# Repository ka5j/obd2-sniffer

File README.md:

# OBD2 CAN Sniffer

A read-only scanner for a car's diagnostic port. It records the messages between the car's computers,
asks the engine computer for live data, trouble codes and the VIN, and shows it all on a laptop. It
only ever asks standard questions, and can't change anything in the car.

Today it runs on an STM32 development board, against a simulated engine computer. The goal is its own
custom circuit board that plugs straight into the car.

## Where it stands

| | |
|---|---|
| **Works today** | On a development board with no car: CAN capture with nothing lost unnoticed, OBD2 live data, trouble codes and VIN, a transmit guard, crash recovery, and a desktop app and command line |
| **Not done yet** | It hasn't been on a real CAN bus or in a real car |
| **The goal** | A custom circuit board that plugs into the car, powered from the laptop, with a hardware switch that turns the transmitter off. It is in design, not built |

The full list is in [Project status](#project-status).

## Try it, no hardware needed

The laptop software includes a simulator of the whole board. You need Python 3.10 or newer (the one
that comes with macOS can be too old: see [Getting started](docs/getting-started.md#level-1-try-it-no-hardware)),
and Git:

```sh
git clone https://github.com/ka5j/obd2-sniffer.git
cd obd2-sniffer
python3 -m venv .venv
source .venv/bin/activate          # Windows: .venv\Scripts\activate
pip install -e "host[gui]"         # the desktop app's Qt library is a large download
obdsniff --port sim gui
```

Press **Connect**, open the **OBD2** tab, and press **Start**.

To go further, with a real board and ready-made firmware, or building from source, see
[Getting started](docs/getting-started.md).

## How it works

A car's computers share one pair of wires, the **CAN bus**, and the **OBD2 port** under the dashboard
is the way in. On the bus, every computer sees every message. So a tool can listen to it all, and ask
the engine computer standard questions such as "what is the engine speed?".

With no car, the development board plays both sides:

```mermaid
flowchart LR
    Laptop["Laptop<br/>desktop app or command line"] <-- "USB cable" --> Tool
    subgraph Board["Development board (NUCLEO-F446RE)"]
        Tool["Scan tool firmware"] <--> CAN["CAN controller<br/>in loopback"]
        ECU["Simulated engine computer"] <--> CAN
    end
```

1. The **laptop** asks one question at a time, and shows the answers.
2. The **firmware** sends each question through its CAN controller, timestamps and numbers every
   message it receives, and sends them to the laptop.
3. The **CAN controller** runs in loopback: it receives its own messages and nothing leaves the chip,
   so a simulated engine computer on the same board can answer through real CAN hardware.

[How it works](docs/how-it-works.md) explains all of this from the beginning, with no car knowledge
assumed.

## Why it's worth a look

- **Nothing is lost unnoticed.** Every message is timestamped to the microsecond and numbered the
  moment it arrives. Measured on the board in loopback: 100,000 messages at 100% network load, none
  lost. When traffic outgrows the USB link, every dropped message is counted and reported.
- **Read-only by design.** The board asks only when the laptop tells it to, and every frame it sends
  passes a transmit guard that allows only read requests, at most 20 a second. Clearing a trouble code
  isn't built in. [The safety design](docs/design/safety.md) adds a hardware switch, and lists the
  risks that remain.
- **Recovers from crashes and says why.** A watchdog restarts the board if the program stops
  responding, and a crash handler records the fault type and code address, then reports them after
  the restart.
- **Tested to safety-critical standards.** The core logic is unit-tested to 100% MC/DC coverage, the
  coverage standard used for flight-control software, and all C code follows the MISRA C:2012 rules
  used in the automotive industry, with every exception documented. See the
  [live quality report](https://ka5j.github.io/obd2-sniffer/).
- **Requirements with a test for each.** What the device must do, survive and never do is written
  down as [numbered requirements](docs/design/requirements.md), each with its test and its honest
  status today.
- **Every release is checked on the board.** The published files are built by CI from the tag, then
  flashed onto the board and checked before they go out.

## Where to go next

| You want to... | Read |
|---|---|
| Understand how it works, from the beginning | [How it works](docs/how-it-works.md) |
| Run it, with or without a board | [Getting started](docs/getting-started.md) |
| Use the desktop app, command line or Python library | [The laptop tool](host/README.md) |
| Judge the engineering | [Safety](docs/design/safety.md), [requirements](docs/design/requirements.md), [testing](docs/design/testing.md) and [how the firmware fits together](docs/design/architecture.md) |
| See the circuit board design | [Circuit board](docs/design/circuit-board.md) and [the design files](hardware/README.md) |
| See every document | [Documentation](docs/README.md) |

## Measured on the board

All of these are in loopback, on a development board.

| What | Result |
|---|---|
| CAN capture, 500 kbit/s at 100% load | 100,000 messages, 0 lost, 0 damaged |
| CAN overload, 1 Mbit/s at 100% load (Release build) | The bus outruns the USB link: 5,209 of 20,000 dropped, each one counted on the board and seen as a gap on the laptop. With streaming off, 0 dropped |
| Commands while the CAN bus is full | 2,623 commands as 42,127 messages arrived, none failed, no byte lost |
| OBD2 against the simulated engine computer | 201 requests in 10 s (the transmit guard allows at most 20 a second), every one answered, 0 timeouts, 0 refused by the guard; none once the laptop stops asking |
| Longest CAN receive interrupt | 6 to 9 µs in the Release build and 10 to 14 µs in Debug across runs, with OBD2 traffic (the time includes serial interrupts that preempt it), against 238 µs between messages at full load |
| Watchdog | A stuck board restarts after 535 ms and reports why |

How each number was measured: [testing.md](docs/design/testing.md#checks-on-the-board).

## Topics covered by this project

| Area | Details |
|---|---|
| Embedded C | Bare-metal firmware on an Arm Cortex-M4, no operating system |
| Microcontroller peripherals | Clocks, UART serial, DMA, timers, interrupts, watchdog, CAN controller |
| Automotive protocols | CAN, OBD2 (SAE J1979), ISO-TP multi-frame transport |
| Reliability | Watchdog, crash capture and reporting, interrupt priorities set by deadline, flow control |
| Safety engineering | Numbered requirements each with a test, a layered read-only safety design with a hardware interlock, failure-mode analysis (FMEA) |
| Python | Desktop app (PySide6), command-line tool, serial communication, board simulator |
| Code quality | MISRA C:2012 compliance with documented deviations, static analysis (cppcheck), worst-case stack analysis |
| Testing and tooling | Unit tests in C (Unity) and Python, 100% MC/DC coverage, sanitizers, CMake, GitHub Actions CI, Git branching workflow |

## Repository layout

| Folder | What's in it |
|---|---|
| [`firmware/`](firmware) | STM32 firmware, one folder per subsystem: `system`, `console`, `can`, `obd`, `fault` (and `hal`, ST's driver settings) |
| [`lib/`](lib) | Portable C with no hardware code: buffers, link encoding, console logic, CAN timing, ISO-TP, OBD2 and the transmit guard. Compiled into the firmware and unit-tested on a laptop |
| [`tests/`](tests) | C unit tests, in the same folders as `lib/` |
| [`host/`](host) | The laptop tool `obdsniff`: command line, desktop app, board simulator |
| [`scripts/`](scripts) | Board check, coverage, MISRA and stack-use gates, quality report, screenshots, release-file and link checks |
| [`hardware/`](hardware/README.md) | Circuit board design files, in KiCad, and the revision A brief. The design isn't started yet |
| [`docs/`](docs) | [All the documents](docs/README.md) |
| [`misra/`](misra) | MISRA policy: every deviation and its reason |

## Project status

| Part | Status |
|---|---|
| Build system, project structure, automated builds (CI) | Done |
| Microcontroller start-up: 168 MHz clock, start-up report, reset-cause reporting | Done, verified on hardware |
| Serial link to the laptop: interrupt and DMA driven, one command protocol, board commands | Done, verified on hardware |
| Watchdog and crash capture with reports after restart | Done, verified on hardware |
| Laptop tool: command line, interactive shell, board simulator | Done, verified on hardware |
| Laptop tool: desktop app with board status, controls and console | Done, verified on hardware |
| Unit tests with 100% MC/DC coverage gate, published test and coverage reports | Done |
| MISRA C:2012 compliance check in CI, published compliance report | Done |
| Worst-case stack use worked out and checked in CI | Done |
| Capturing CAN messages and streaming them to the laptop | Done (tested in loopback), verified on hardware |
| OBD2 requests: live data, VIN, trouble codes, from a simulated engine computer in loopback | Done, verified on hardware |
| Transmit guard: only read requests, rate limited, sent only when the laptop asks | Done (tested in loopback), verified on hardware |
| Requirements, read-only safety design, failure-mode analysis, circuit board design | Done (written down; see [Documentation](docs/README.md)) |
| Real CAN bus on the desk with two transceivers, bus fault tests | Not started |
| USB straight from the microcontroller, with no programmer chip in between | Not started |
| Silent bit-rate detection and the bus-error latch | Not started |
| Circuit board revision A: schematic, layout, bring-up | In design: schematic checked, parts placed on the board, routing next |
| Testing in a real car | Not started |
| Circuit board revision B: the device that plugs into the car | Not started |

## License

MIT. See [LICENSE](LICENSE).

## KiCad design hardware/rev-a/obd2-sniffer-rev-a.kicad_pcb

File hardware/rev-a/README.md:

# Revision A: working brief

Part of the [project documentation](../../docs/README.md). The folder's guide is [here](../README.md), and
[the circuit board](../../docs/design/circuit-board.md) explains why each block exists.

**Status: parts placed on the board, nothing routed.** The schematic is drawn and its
[review](schematic-review.md) found no wiring error. The [board](#the-board) has its outline, layers, rules and every
part placed, with no copper tracks yet. Three datasheets are still unread and no one outside the project has reviewed
the design.

The schematic can be read without KiCad in [obd2-sniffer-rev-a.pdf](obd2-sniffer-rev-a.pdf), which is exported from
the KiCad files each time they change.

## In short

Revision A is the first board, built for bring-up and testing rather than to be small. It has room to probe, test points
on every important signal, and a debug header. Its mistakes get fixed in revision B, the finished plug-in device.

This page is the working sheet: the decisions, the parts and the datasheet each one was checked against, the pins, and
the checklist to complete before ordering. Everything on it can change, except the safety rules.

## Decisions

| Decision | Choice | Reason |
|---|---|---|
| Power | USB only. No connection to the car's 12 V (OBD2 pin 16) | The board only works with a laptop attached, and the laptop supplies 5 V. Removes the battery voltage from the board |
| CAN transceiver | One with a silent pin, not a standby pin | Silent mode keeps the receiver fully working with the transmitter off. A standby pin would stop normal receiving too |
| Silent-pin default | A 4.7 k resistor to 3.3 V on the board | The transceiver's internal resistor pulls the pin low, which selects "able to transmit". The board's resistor has to win, also against the microcontroller's own 30 to 50 k pull-down if firmware turned it on by mistake: the signal then still sits at 2.8 V, above the 2.31 V the transceiver needs |
| Silent signal | One signal for both transceivers | The self-test then needs the switch in OBD, which also tests the switch. One pin, one light |
| TX light | Switched by a transistor from the silent signal, through a 100 k gate resistor | The light can't load the signal, and can't be lit by firmware alone. The resistor keeps a short inside the transistor from pulling the signal low |
| Self-test connection | CAR/TEST jumpers: two 3-pin headers, one for each bus wire, placed apart | CAN2 can't reach the car connector in any position. One 2 x 3 block was rejected: a jumper cap put on sideways would short the car's two CAN wires together |
| Termination | CAN1: solder jumper, open by default. CAN2: fitted | The car's bus has its own. The self-test bus uses CAN2's |
| USB fuse | A chip fuse, not a resettable one | Lower resistance, so the transceivers' 5 V stays above their 4.5 V minimum |
| Car connector | 3 screw terminals: CANH, CANL, ground | Wiring can be checked. There is no terminal for pin 16 |

## Blocks and requirements

Every part on the board has to trace to a [requirement](../../docs/design/requirements.md).

| Block | Serves | Schematic drawn? |
|---|---|---|
| USB-C: power, fuse, data and ESD protection | PWR-5, LNK-3, USE-4 | Yes: `usb-power.kicad_sch` |
| 3.3 V regulator, PWR light | PWR-5, USE-3 | Yes: `usb-power.kicad_sch` |
| Microcontroller: crystal, decoupling, reset, BOOT0, SWD header | USE-4 | Yes: `microcontroller.kicad_sch` |
| CAN1 transceiver, ESD protection, termination solder jumper, car connector | CAN-1, CAN-6, PWR-8 | Yes: `can.kicad_sch` |
| CAN2 transceiver and CAR/TEST jumpers | CAN-7 | Yes: `can.kicad_sch` |
| LISTEN/OBD switch, silent signal, TX light | SAF-3, USE-3 | Yes: `can.kicad_sch` |
| BUS light | USE-3 | Yes: `microcontroller.kicad_sch` |
| Test points, debug serial header | Revision A only | Yes: on all three sheets |

## Parts

"Read" means the maker's datasheet was read for this design and the values below come from it.

| Part | Number | Why this one | Datasheet | Read? |
|---|---|---|---|---|
| Microcontroller | STM32F446RET6, LQFP64 | Same chip as the development board | [ST, DS10693 rev. 11](https://www.st.com/resource/en/datasheet/stm32f446re.pdf), with application notes AN4488 rev. 7, AN2606 rev. 71 and AN2867 rev. 25 | Yes |
| CAN transceiver, 2 of | TJA1051T/3, SO8 | Silent pin; 3.3 V logic supply; bus pins withstand -58 to +58 V; transmit timeout 0.3 to 5 ms; disconnects from the bus when unpowered (leakage at most 5 µA) | [NXP, rev. 9](https://www.nxp.com/docs/en/data-sheet/TJA1051.pdf) | Yes |
| CAN ESD protection | NUP2105L, SOT-23 | Working voltage 24 V and breakdown at least 26.2 V, so a short to a 16 V battery doesn't make it conduct; 30 kV contact ESD | [onsemi, rev. 12](https://www.onsemi.com/pdf/datasheet/nup2105l-d.pdf) | Yes |
| 3.3 V regulator | AP2112K-3.3, SOT-23-5 | 600 mA; input up to 6.5 V absolute; stable with 1 µF ceramic capacitors in and out | [Diodes, rev. 2-2](https://www.diodes.com/assets/Datasheets/AP2112.pdf) | Yes |
| USB ESD protection | USBLC6-2SC6, SOT-23-6 | Made for USB data pairs: at most 3.5 pF per line, 8 kV contact ESD, and it protects the 5 V line too | [ST, DS4260 rev. 7](https://www.st.com/resource/en/datasheet/usblc6-2.pdf) | Yes |
| USB-C socket | GCT USB4105-GF-A, 16 pins | USB 2.0 pins only; VBUS contacts rated 5 A together; 20,000 matings; a footprint ships with KiCad | [GCT](https://gct.co/files/drawings/usb4105.pdf) | Yes |
| USB fuse | Bourns SF-1206F100-2, 1 A fast, 1206 | 0.132 ohm typical, so about 35 mV lost at 250 mA; rated 63 V, interrupts 50 A | [Bourns](https://www.bourns.com/docs/product-datasheets/sf-1206f.pdf) | Yes |
| Resistors, capacitors, PWR light | 0603 (4.7 µF: 0805), capacitors X7R 16 V | Large enough to rework by hand on a test board | | |
| Crystal | ECS ECS-80-10-30B-TR: 8 MHz, 10 pF load, 5.0 x 3.2 mm | At most 100 ohm, where 3.2 x 2.5 mm crystals at 8 MHz reach 400 ohm; pads 2 and 4 are ground | [ECS](https://ecsxtal.com/store/pdf/ECX-53B.pdf) | Yes |
| Reset and boot buttons | C&K PTS645 type, 6 mm | A footprint ships with KiCad | | Not yet: read when the footprint is checked at layout |
| TX light transistor | onsemi BSS84, SOT-23 | P-channel; gate leakage at most 10 nA, so it doesn't load the silent signal; turns on between 0.8 and 2.0 V below 3.3 V | [onsemi, rev. 5](https://www.onsemi.com/pdf/datasheet/bss84-d.pdf) | Yes |
| LISTEN/OBD switch | C&K JS102011SAQN slide switch | Two positions; a footprint ships with KiCad | | Not yet. The schematic assumes pin 2 is the common pin and that it breaks one contact before making the other |
| Car connector | Phoenix Contact MKDS 1,5/3-5,08, 3 screw terminals | A footprint ships with KiCad | | Not yet |
| CAR/TEST and other headers | 2.54 mm pin headers, with two jumper caps | | | |

**Figures the design relies on, from the datasheets read**

| Figure | Value | Used for |
|---|---|---|
| TJA1051 silent pin | High is silent, low is normal. Internal pull-down, 1 to 10 µA at the pin | The board's pull-up and the switch |
| TJA1051 supply | 4.5 to 5.5 V. Below its undervoltage level (3.5 to 4.5 V) it disconnects from the bus | The 5 V budget from USB |
| TJA1051 supply current | At most 70 mA each while sending a dominant bit, 10 mA idle | The USB power budget |
| TJA1051 logic supply | 2.8 to 5.5 V | Runs from the 3.3 V rail |
| USB 5 V budget | 4.75 V at the laptop's port, less the cable, socket and fuse: about 4.6 V at the transceivers, against their 4.5 V minimum | Choosing a low-resistance fuse. On a weak port the transceivers disconnect from the bus, which is the safe direction |
| TX light against the silent pin | The transceiver is certainly silent above 2.31 V and certainly able to transmit below 0.99 V. The light is certainly on below 1.3 V | Between about 1.3 and 2.3 V the board could be able to transmit with the light dark. The signal is driven to 0 or 3.3 V, and no single fault found leaves it in between (fault table in the pull request that added the CAN sheet) |
| AP2112 heat | 184 °C/W in SOT-23-5 | (5.25 - 3.3) V at the worst-case 120 mA is 0.23 W, about 43 °C of rise |
| Charge taken at plug-in | About 42 µC if every capacitor on the board charges at once, against 50 µC (10 µF at 5 V) allowed by USB 2.0 | C1 on the 5 V rail is 1 µF, not 4.7 µF ([schematic review](schematic-review.md#charge-taken-at-plug-in)) |
| STM32F446 core capacitor | LQFP64 has one VCAP pin: a single 4.7 µF ceramic, ESR under 1 ohm | The microcontroller sheet. Larger packages use two 2.2 µF instead |
| STM32F446 decoupling | 100 nF at each VDD pin plus one 4.7 µF; 100 nF plus 1 µF on VDDA; VBAT to VDD with 100 nF; 100 nF on NRST | The microcontroller sheet |
| STM32F446 crystal | 4 to 26 MHz. The crystal's critical gain must stay under 1 mA/V | Choosing the crystal and its load capacitors |
| Crystal start-up margin | Critical gain 4 x 100 ohm x (2 pi x 8 MHz)^2 x (5 pF + 10 pF)^2 = 0.23 mA/V, against the chip's 1 mA/V limit: a margin of about 22, where ST asks for 5 or more | Choosing the crystal. An 18 pF crystal of 400 ohm would have failed this check |
| Crystal load capacitors | 2 x (10 pF load - 5 pF stray) = 10 pF each. The stray figure is an estimate | Checked on the built board by measuring the clock |
| STM32F446 USB bootloader | Needs a crystal that is a whole number of MHz, and prefers a low one such as 8 MHz. Entered with BOOT0 high and PB2 low. No pull-up resistor needed on the data lines | The 8 MHz crystal, the BOOT0 button and a pull-down on PB2 |
| STM32F446 bootloader pins | In bootloader mode the chip drives or pulls PA4 to PA10, PB5, PB6, PB9 to PB15, PC7 and PC9 to PC11 | The silent-signal pin must not be one of these, or the bootloader could enable the transmitter |

## Bill of materials

Exported from the schematic with `kicad-cli sch export bom`: 52 parts on 28 lines. Capacitors are X7R, 16 V, unless marked.
A blank maker means any maker's part of that value and size. The ten test-point pads and the solder jumper are
copper shapes on the board, not parts, so they aren't listed.

| Parts | Count | Value | KiCad footprint | Maker and part number |
|---|---|---|---|---|
| C1, C2, C3, C11 | 4 | 1uF 16V | `C_0603_1608Metric` |  |
| C4, C5, C6, C7, C9, C10, C15, C16, C17, C18, C19 | 11 | 100nF | `C_0603_1608Metric` |  |
| C8, C12 | 2 | 4.7uF 16V | `C_0805_2012Metric` |  |
| C13, C14 | 2 | 10pF C0G | `C_0603_1608Metric` |  |
| D1 | 1 | Green, PWR | `LED_0603_1608Metric` |  |
| D2 | 1 | Yellow, BUS | `LED_0603_1608Metric` |  |
| D3 | 1 | Red, TX | `LED_0603_1608Metric` |  |
| D4 | 1 | NUP2105L | `SOT-23` | onsemi NUP2105LT1G |
| F1 | 1 | 1A fast | `Fuse_1206_3216Metric` | Bourns SF-1206F100-2 |
| J1 | 1 | USB4105-GF-A | `USB_C_Receptacle_GCT_USB4105-xx-A_16P_TopMnt_Horizontal` | GCT USB4105-GF-A |
| J2 | 1 | Pin header | `PinHeader_1x06_P2.54mm_Vertical` |  |
| J3, JP1, JP2 | 3 | Pin header | `PinHeader_1x03_P2.54mm_Vertical` |  |
| J4 | 1 | CANH CANL GND | `TerminalBlock_Phoenix_MKDS-1,5-3-5.08_1x03_P5.08mm_Horizontal` | Phoenix Contact MKDS 1,5/3-5,08 |
| Q1 | 1 | BSS84 | `SOT-23` | onsemi BSS84 |
| R1, R2 | 2 | 5.1k | `R_0603_1608Metric` |  |
| R3, R6, R8 | 3 | 1k | `R_0603_1608Metric` |  |
| R4, R5 | 2 | 10k | `R_0603_1608Metric` |  |
| R7 | 1 | 4.7k | `R_0603_1608Metric` |  |
| R9, R10 | 2 | 120R | `R_0805_2012Metric` |  |
| R11 | 1 | 100k | `R_0603_1608Metric` |  |
| SW1, SW2 | 2 | Push button | `SW_SPST_PTS645Sx43SMTR92` |  |
| SW3 | 1 | LISTEN/OBD | `SW_SPDT_CK_JS102011SAQN` | C&K JS102011SAQN |
| TP11 | 1 | Test point, wire loop | `TestPoint_Loop_D2.50mm_Drill1.0mm` |  |
| U1 | 1 | USBLC6-2SC6 | `SOT-23-6` | STMicroelectronics USBLC6-2SC6 |
| U2 | 1 | AP2112K-3.3 | `SOT-23-5` | Diodes Incorporated AP2112K-3.3TRG1 |
| U3 | 1 | STM32F446RET6 | `LQFP-64_10x10mm_P0.5mm` | STMicroelectronics STM32F446RET6 |
| U4, U5 | 2 | TJA1051T/3 | `SOIC-8_3.9x4.9mm_P1.27mm` | NXP TJA1051T/3 |
| Y1 | 1 | 8MHz 10pF | `Crystal_SMD_5032-4Pin_5.0x3.2mm` | ECS ECS-80-10-30B-TR |

## The board

| Item | Choice | Reason |
|---|---|---|
| Size | 80 x 56 mm, corners rounded at 2 mm, four M3 mounting holes | Room to probe. Standoffs keep the pins underneath off the desk |
| Layers | 4, 1.6 mm thick. Planned use: signals, ground, power, signals | A solid ground layer under the USB and CAN signals |
| Parts | All on the top side | One assembly pass, and nothing hidden when probing |
| Smallest track and gap | 0.15 mm | Any board maker can build it. The chosen maker's own rules are confirmed before ordering |
| Smallest via | 0.6 mm with a 0.3 mm hole | Same |
| Copper to board edge | 0.3 mm | Same |

**Where things are, and why**

| Area | Parts | Reason |
|---|---|---|
| Left edge | USB-C socket, its ESD protection right behind it | A discharge is clamped at the connector. The microcontroller is turned so its USB pins face the socket |
| Top left | Fuse, 3.3 V regulator, PWR light | Power comes in at the left and flows right |
| Centre | Microcontroller, a capacitor beside each supply pin, the crystal beside its two pins | Short paths for the supply and the clock |
| Top edge | SWD and debug serial headers | Reachable with the board flat on a desk |
| Bottom edge | BOOT and RESET buttons, LISTEN/OBD switch with the TX light beside it | The switch's lever overhangs the edge. The light sits next to the control it reports on |
| Right | The two transceivers, CAR/TEST headers, ESD protection, screw terminal on the edge | The car side is kept together and away from USB. The two CAR/TEST headers are 5.5 mm apart, so one jumper cap can't bridge them |

**Checks on the board file**

| Check | Result |
|---|---|
| Board against schematic (`kicad-cli pcb drc --schematic-parity`) | 0 differences |
| Overlapping parts, clearances, holes | 0 violations |
| Connections not yet routed | 150, as expected before routing |
| Silkscreen | 19 warnings: part labels overlap each other or the board edge. Labels are arranged in the last layout step |
| Footprints against each datasheet's pad drawing | Not done yet |

One rule is relaxed, in `obd2-sniffer-rev-a.kicad_dru`: the USB-C socket's two locating pegs sit 0.19 mm from its own
ground pads, which is how GCT's pad drawing for the part has them. Every other hole keeps 0.25 mm.

The switch's position at the edge is taken from KiCad's footprint, because its datasheet is still unread.

## Microcontroller pins

Pin numbers are for LQFP64. Each was checked in ST's datasheet (table 10) and matches KiCad's symbol for the chip.

| Function | Pin (LQFP64 number) | Where it comes from |
|---|---|---|
| CAN1 receive, transmit | PB8 (61), PB9 (62) | Used by the firmware today ([`board.h`](../../firmware/system/board.h)) |
| Debug serial TX, RX (USART2) | PA2 (16), PA3 (17) | Used by the firmware today ([`board.h`](../../firmware/system/board.h)) |
| CAN2 receive, transmit | PB12 (33), PB13 (34) | Reserved ([pin assignments](../../docs/design/hardware.md#pin-assignments)) |
| USB data D-, D+ | PA11 (44), PA12 (45) | Fixed by the chip's USB peripheral |
| SWD debug SWDIO, SWCLK | PA13 (46), PA14 (49) | Fixed by the chip |
| Crystal in, out | PH0 (5), PH1 (6) | Fixed by the chip |
| BOOT0, BOOT1, reset | BOOT0 (60), PB2 (28), NRST (7) | Fixed by the chip |
| Silent-signal control | PC6 (37) | Chosen: the bootloader leaves it alone, so it floats and the board's pull-up keeps the transceivers silent |
| BUS light | PC8 (39) | Chosen: not used by the bootloader |

## What the firmware will need for this board

None of it is built yet.

- **Crystal:** the firmware expects an 8 MHz clock from the development board's programmer. An 8 MHz crystal needs one
  setting changed ([clock tree](../../docs/design/build-and-boot.md#clock-tree)).
- **Pins:** a board definition for revision A beside the development board's.
- **New drivers:** native USB, CAN2, the silent-signal control and the BUS light.
- **USB:** the board has no VBUS signal on PA9, so the USB driver must not wait for one. It must declare the current
  the board draws: 340 mA at worst.
- **No user button:** the development board's button goes away, along with its event.

## Before ordering

**The design**
- [ ] ERC and DRC pass, and every exclusion has a written reason ([design checks](../README.md#design-checks))
- [ ] Every part in the table above has a reason and a read datasheet, and is in stock
- [x] Every microcontroller pin in the schematic matches the pin table above
- [ ] Every footprint checked against its datasheet, and the board checked in KiCad's 3D view
- [ ] Reviewed by someone outside the project

**The safety rules** ([safety.md](../../docs/design/safety.md))
- [ ] No net on the board connects to OBD2 pin 16, and the car connector has only CANH, CANL and ground
- [ ] The silent signal is pulled to silent on the board, so a reset, crash or blank chip means silent
- [ ] In LISTEN, the switch stops the firmware enabling the transmitter, however the firmware behaves
- [ ] The TX light is switched by the silent signal itself, not by firmware
- [ ] CAN1's transceiver has a dominant timeout, and its bus pins withstand a short to the car's battery
- [ ] CAN1's termination is open by default
- [ ] No position of the CAR/TEST jumpers connects CAN2 to the car connector

**The rule for ordering**
- [ ] [The conditions for ordering boards](../README.md#before-ordering-any-boards) are met

## Errata

Mistakes found on the built board go in `ERRATA.md` in this folder, so revision B can fix them.

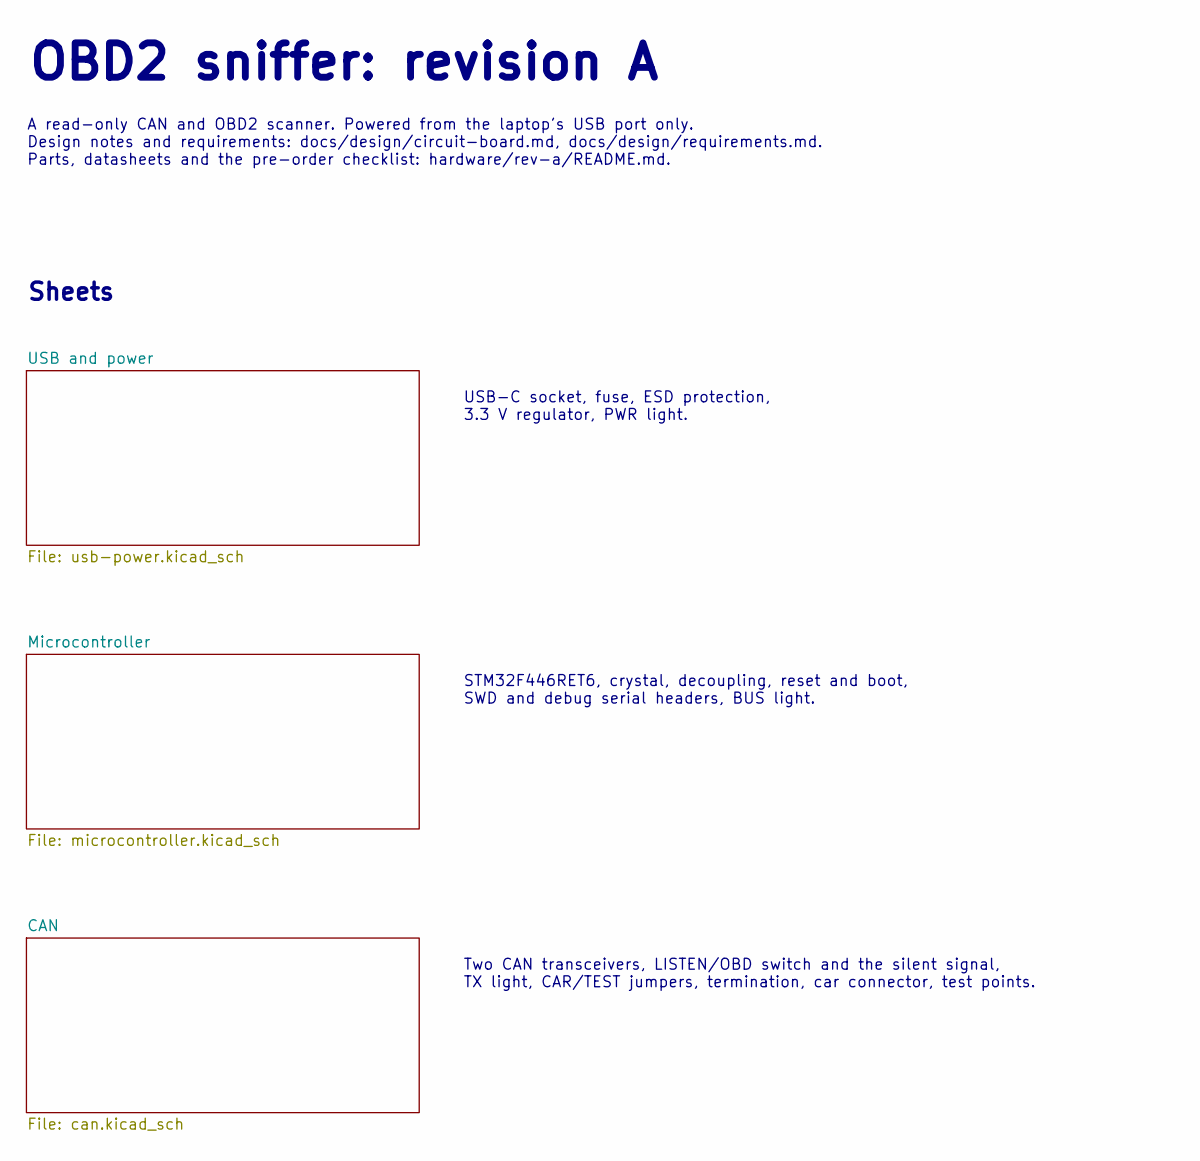
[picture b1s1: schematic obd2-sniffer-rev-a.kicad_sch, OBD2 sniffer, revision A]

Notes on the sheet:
USB-C socket, fuse, ESD protection, 3.3 V regulator, PWR light.
STM32F446RET6, crystal, decoupling, reset and boot, SWD and debug serial headers, BUS light.
OBD2 sniffer: revision A
Sheets
Two CAN transceivers, LISTEN/OBD switch and the silent signal, TX light, CAR/TEST jumpers, termination, car connector, test points.
A read-only CAN and OBD2 scanner. Powered from the laptop's USB port only. Design notes and requirements: docs/design/circuit-board.md, docs/design/requirements.md. Parts, datasheets and the pre-order checklist: hardware/rev-a/README.md.

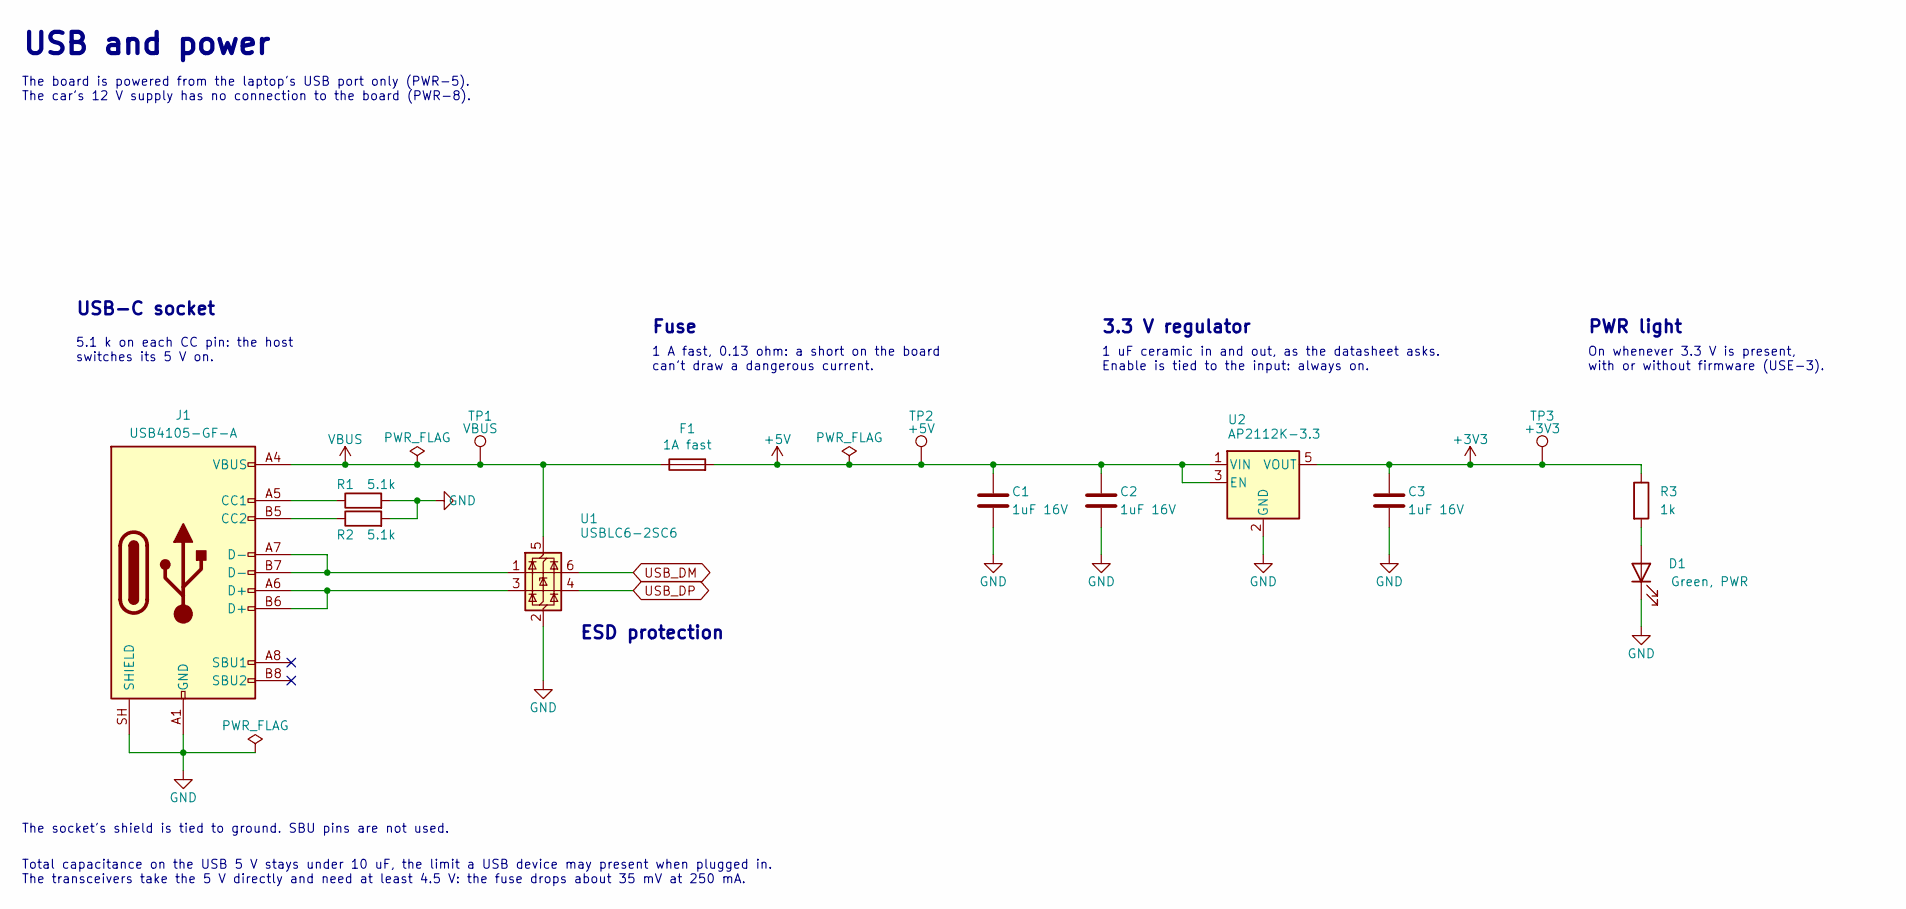
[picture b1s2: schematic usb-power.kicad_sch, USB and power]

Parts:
C1, C2, C3: 1uF 16V; C_0603_1608Metric
D1: Green, PWR; LED_0603_1608Metric
F1: 1A fast; Fuse_1206_3216Metric; MPN SF-1206F100-2
J1: USB4105-GF-A; USB_C_Receptacle_GCT_USB4105-xx-A_16P_TopMnt_Horizontal; MPN USB4105-GF-A
R1, R2: 5.1k; R_0603_1608Metric
R3: 1k; R_0603_1608Metric
TP1: VBUS; TestPoint_Pad_D1.5mm
TP2: +5V; TestPoint_Pad_D1.5mm
TP3: +3V3; TestPoint_Pad_D1.5mm
U1: USBLC6-2SC6; SOT-23-6; MPN USBLC6-2SC6
U2: AP2112K-3.3; SOT-23-5; MPN AP2112K-3.3TRG1

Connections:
+3V3: C3.1, R3.1, TP3.1, U2.5 (VOUT); also elsewhere on the board
+5V: C1.1, C2.1, F1.2, TP2.1, U2.1 (VIN), U2.3 (EN); also elsewhere on the board
GND: C1.2, C2.2, C3.2, D1.1 (K), J1.A1 (GND), J1.A12 (GND), J1.B1 (GND), J1.B12 (GND), J1.SH (SHIELD), R1.2, R2.2, U1.2 (GND), U2.2 (GND); also elsewhere on the board
unnamed: D1.2 (A), R3.2
unnamed: J1.A5 (CC1), R1.1
unnamed: J1.B5 (CC2), R2.1
unnamed: J1.A6 (D+), J1.B6 (D+), U1.3 (I/O2)
unnamed: J1.A7 (D-), J1.B7 (D-), U1.1 (I/O1)
USB_DM: U1.6 (I/O1); also elsewhere on the board
USB_DP: U1.4 (I/O2); also elsewhere on the board
VBUS: F1.1, J1.A4 (VBUS), J1.A9 (VBUS), J1.B4 (VBUS), J1.B9 (VBUS), TP1.1, U1.5 (VBUS)

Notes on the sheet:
The board is powered from the laptop's USB port only (PWR-5). The car's 12 V supply has no connection to the board (PWR-8).
Total capacitance on the USB 5 V stays under 10 uF, the limit a USB device may present when plugged in. The transceivers take the 5 V directly and need at least 4.5 V: the fuse drops about 35 mV at 250 mA.
On whenever 3.3 V is present, with or without firmware (USE-3).
ESD protection
USB and power
PWR light
USB-C socket
5.1 k on each CC pin: the host switches its 5 V on.
The socket's shield is tied to ground. SBU pins are not used.
1 A fast, 0.13 ohm: a short on the board can't draw a dangerous current.
1 uF ceramic in and out, as the datasheet asks. Enable is tied to the input: always on.
Fuse
3.3 V regulator

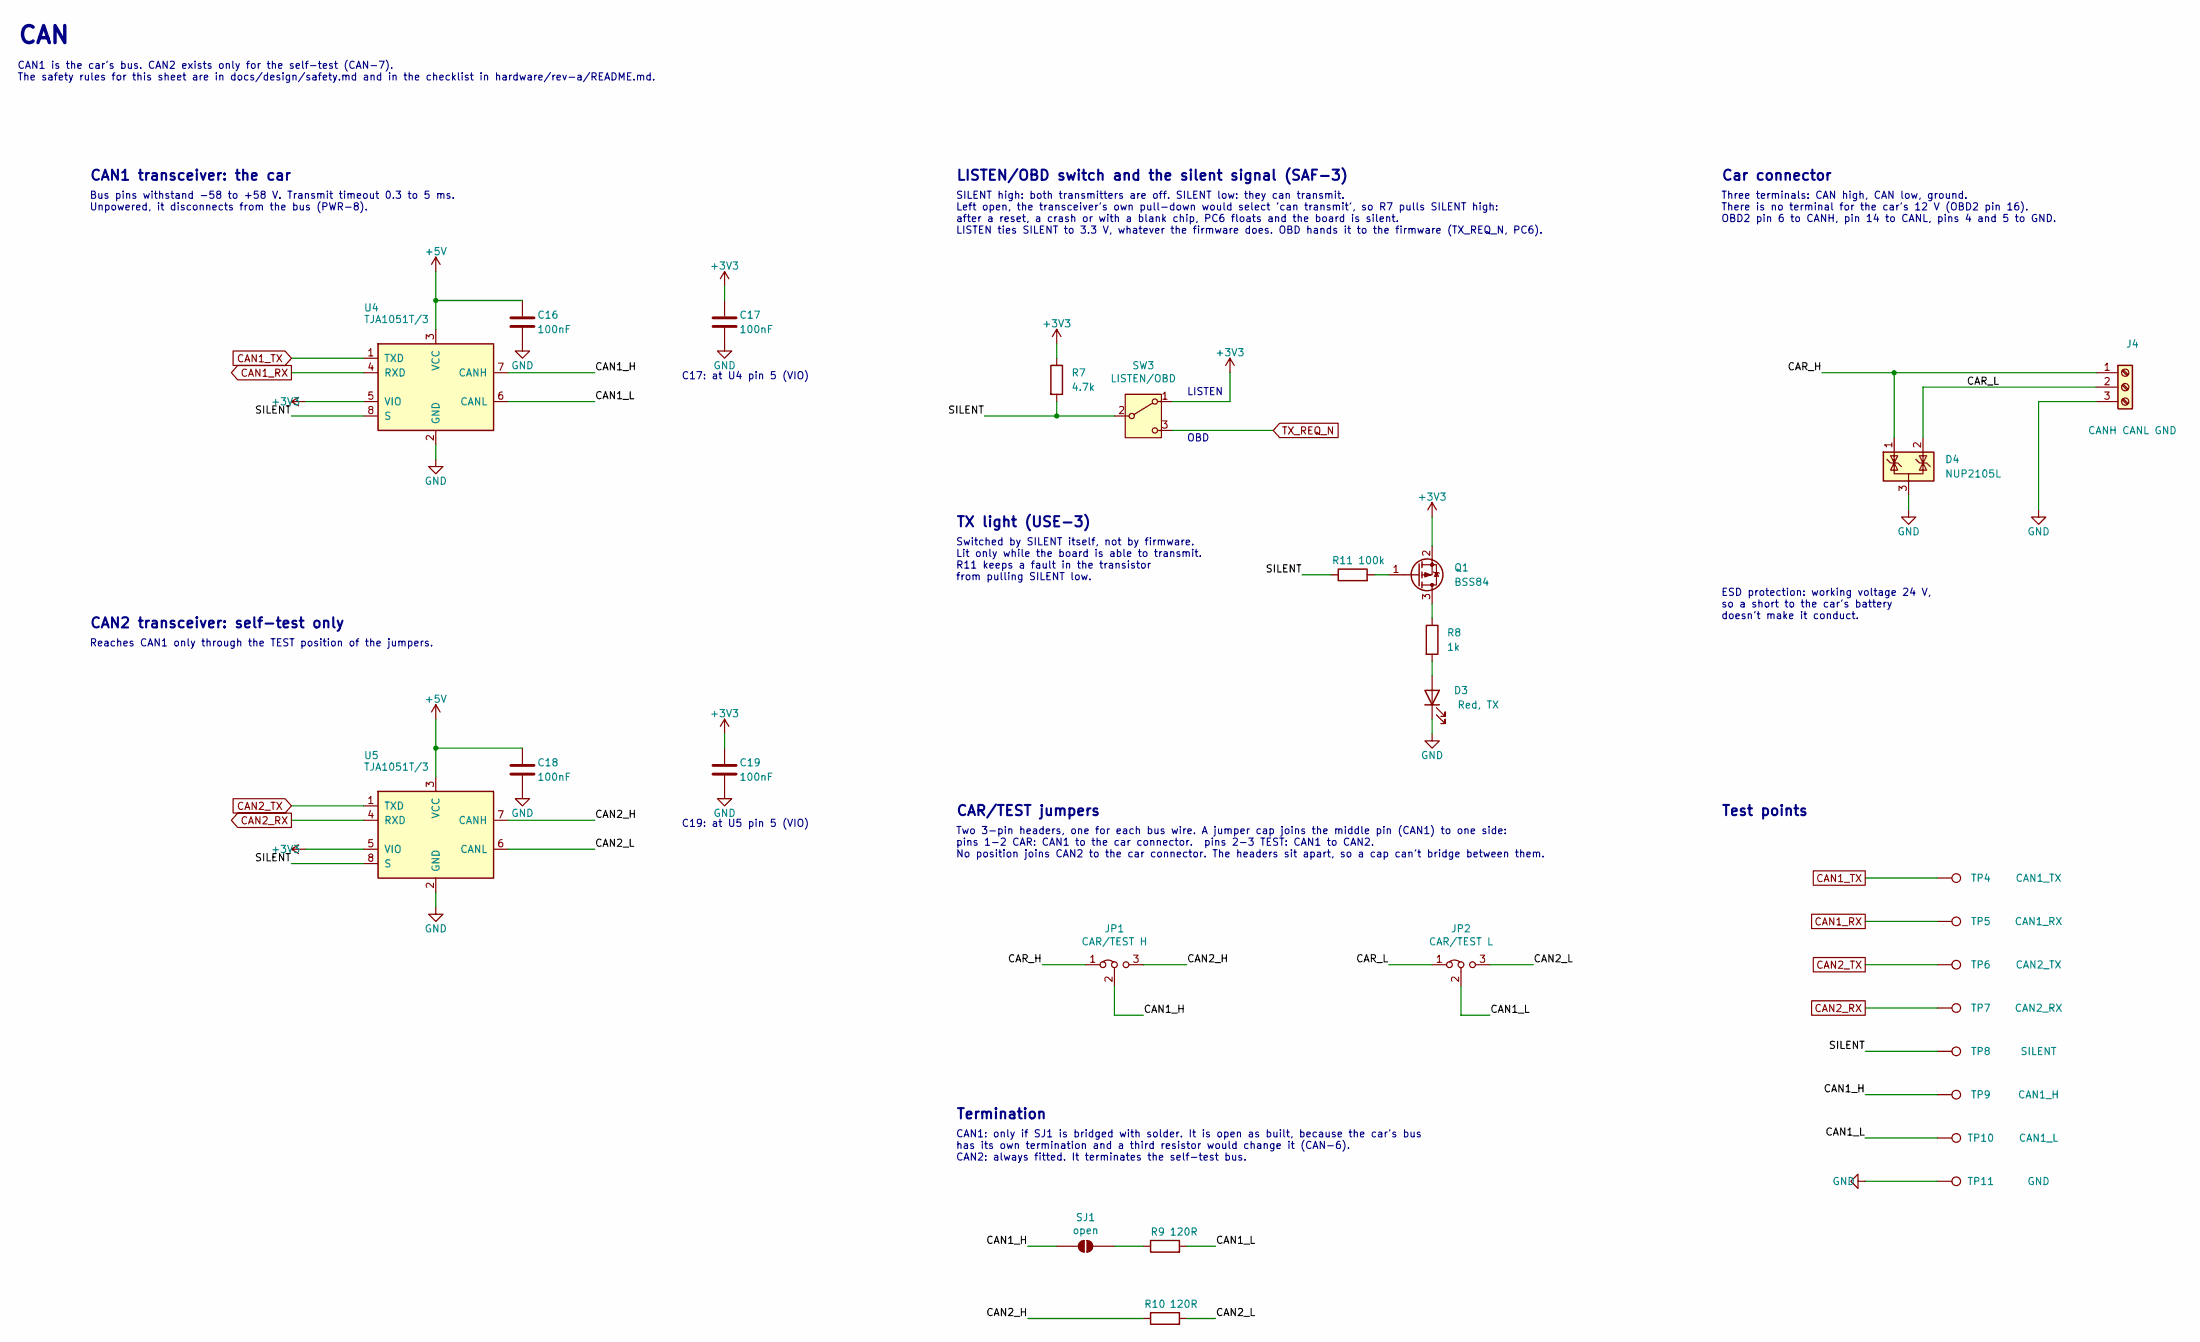
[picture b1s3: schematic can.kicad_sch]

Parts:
C16, C17, C18, C19: 100nF; C_0603_1608Metric
D3: Red, TX; LED_0603_1608Metric
D4: NUP2105L; SOT-23; MPN NUP2105LT1G
J4: CANH CANL GND; TerminalBlock_Phoenix_MKDS-1,5-3-5.08_1x03_P5.08mm_Horizont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; MPN MKDS 1,5/3-5,08
JP1: CAR/TEST H; PinHeader_1x03_P2.54mm_Vertical
JP2: CAR/TEST L; PinHeader_1x03_P2.54mm_Vertical
Q1: BSS84; SOT-23; MPN BSS84
R7: 4.7k; R_0603_1608Metric
R8: 1k; R_0603_1608Metric
R9, R10: 120R; R_0805_2012Metric
R11: 100k; R_0603_1608Metric
SJ1: open; SolderJumper-2_P1.3mm_Open_RoundedPad1.0x1.5mm
SW3: LISTEN/OBD; SW_SPDT_CK_JS102011SAQN; MPN JS102011SAQN
TP4: CAN1_TX; TestPoint_Pad_D1.5mm
TP5: CAN1_RX; TestPoint_Pad_D1.5mm
TP6: CAN2_TX; TestPoint_Pad_D1.5mm
TP7: CAN2_RX; TestPoint_Pad_D1.5mm
TP8: SILENT; TestPoint_Pad_D1.5mm
TP9: CAN1_H; TestPoint_Pad_D1.5mm
TP10: CAN1_L; TestPoint_Pad_D1.5mm
TP11: GND; TestPoint_Loop_D2.50mm_Drill1.0mm
U4, U5: TJA1051T/3; SOIC-8_3.9x4.9mm_P1.27mm; MPN TJA1051T/3

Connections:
+3V3: C17.1, C19.1, Q1.2 (S), R7.1, SW3.1 (A), U4.5 (VIO), U5.5 (VIO); also elsewhere on the board
+5V: C16.1, C18.1, U4.3 (VCC), U5.3 (VCC); also elsewhere on the board
/CAN/CAN1_H: JP1.2 (C), SJ1.1 (A), TP9.1, U4.7 (CANH)
/CAN/CAN1_L: JP2.2 (C), R9.2, TP10.1, U4.6 (CANL)
/CAN/CAN2_H: JP1.3 (B), R10.1, U5.7 (CANH)
/CAN/CAN2_L: JP2.3 (B), R10.2, U5.6 (CANL)
/CAN/CAR_H: D4.1 (K), J4.1, JP1.1 (A)
/CAN/CAR_L: D4.2 (K), J4.2, JP2.1 (A)
/CAN/SILENT: R7.2, R11.1, SW3.2 (B), TP8.1, U4.8 (S), U5.8 (S)
CAN1_RX: TP5.1, U4.4 (RXD); also elsewhere on the board
CAN1_TX: TP4.1, U4.1 (TXD); also elsewhere on the board
CAN2_RX: TP7.1, U5.4 (RXD); also elsewhere on the board
CAN2_TX: TP6.1, U5.1 (TXD); also elsewhere on the board
GND: C16.2, C17.2, C18.2, C19.2, D3.1 (K), D4.3 (A), J4.3, TP11.1, U4.2 (GND), U5.2 (GND); also elsewhere on the board
unnamed: D3.2 (A), R8.2
unnamed: Q1.3 (D), R8.1
unnamed: Q1.1 (G), R11.2
unnamed: R9.1, SJ1.2 (B)
TX_REQ_N: SW3.3 (C); also elsewhere on the board

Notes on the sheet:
Three terminals: CAN high, CAN low, ground. There is no terminal for the car's 12 V (OBD2 pin 16). OBD2 pin 6 to CANH, pin 14 to CANL, pins 4 and 5 to GND.
CAN1: only if SJ1 is bridged with solder. It is open as built, because the car's bus has its own termination and a third resistor would change it (CAN-6). CAN2: always fitted. It terminates the self-test bus.
Termination
SILENT high: both transmitters are off. SILENT low: they can transmit. Left open, the transceiver's own pull-down would select 'can transmit', so R7 pulls SILENT high: after a reset, a crash or with a blank chip, PC6 floats and the board is silent. LISTEN ties SILENT to 3.3 V, whatever the firmware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
Bus pins withstand -58 to +58 V. Transmit timeout 0.3 to 5 ms. Unpowered, it disconnects from the bus (PWR-8).
Switched by SILENT itself, not by firmware. Lit only while the board is able to transmit. R11 keeps a fault in the transistor from pulling SILENT low.
LISTEN
Two 3-pin headers, one for each bus wire. A jumper cap joins the middle pin (CAN1) to one side: pins 1-2 CAR: CAN1 to the car connector. pins 2-3 TEST: CAN1 to CAN2. No position joins CAN2 to the car connector. The headers sit apart, so a cap can't bridge between them.
C17: at U4 pin 5 (VIO)
CAR/TEST jumpers
CAN1 is the car's bus. CAN2 exists only for the self-test (CAN-7). The safety rules for this sheet are in docs/design/safety.md and in the checklist in hardware/rev-a/README.md.
CAN2 transceiver: self-test only
CAN1 transceiver: the car
Reaches CAN1 only through the TEST position of the jumpers.
TX light (USE-3)
ESD protection: working voltage 24 V, so a short to the car's battery doesn't make it conduct.
OBD
Car connector
CAN
Test points
LISTEN/OBD switch and the silent signal (SAF-3)
C19: at U5 pin 5 (VIO)

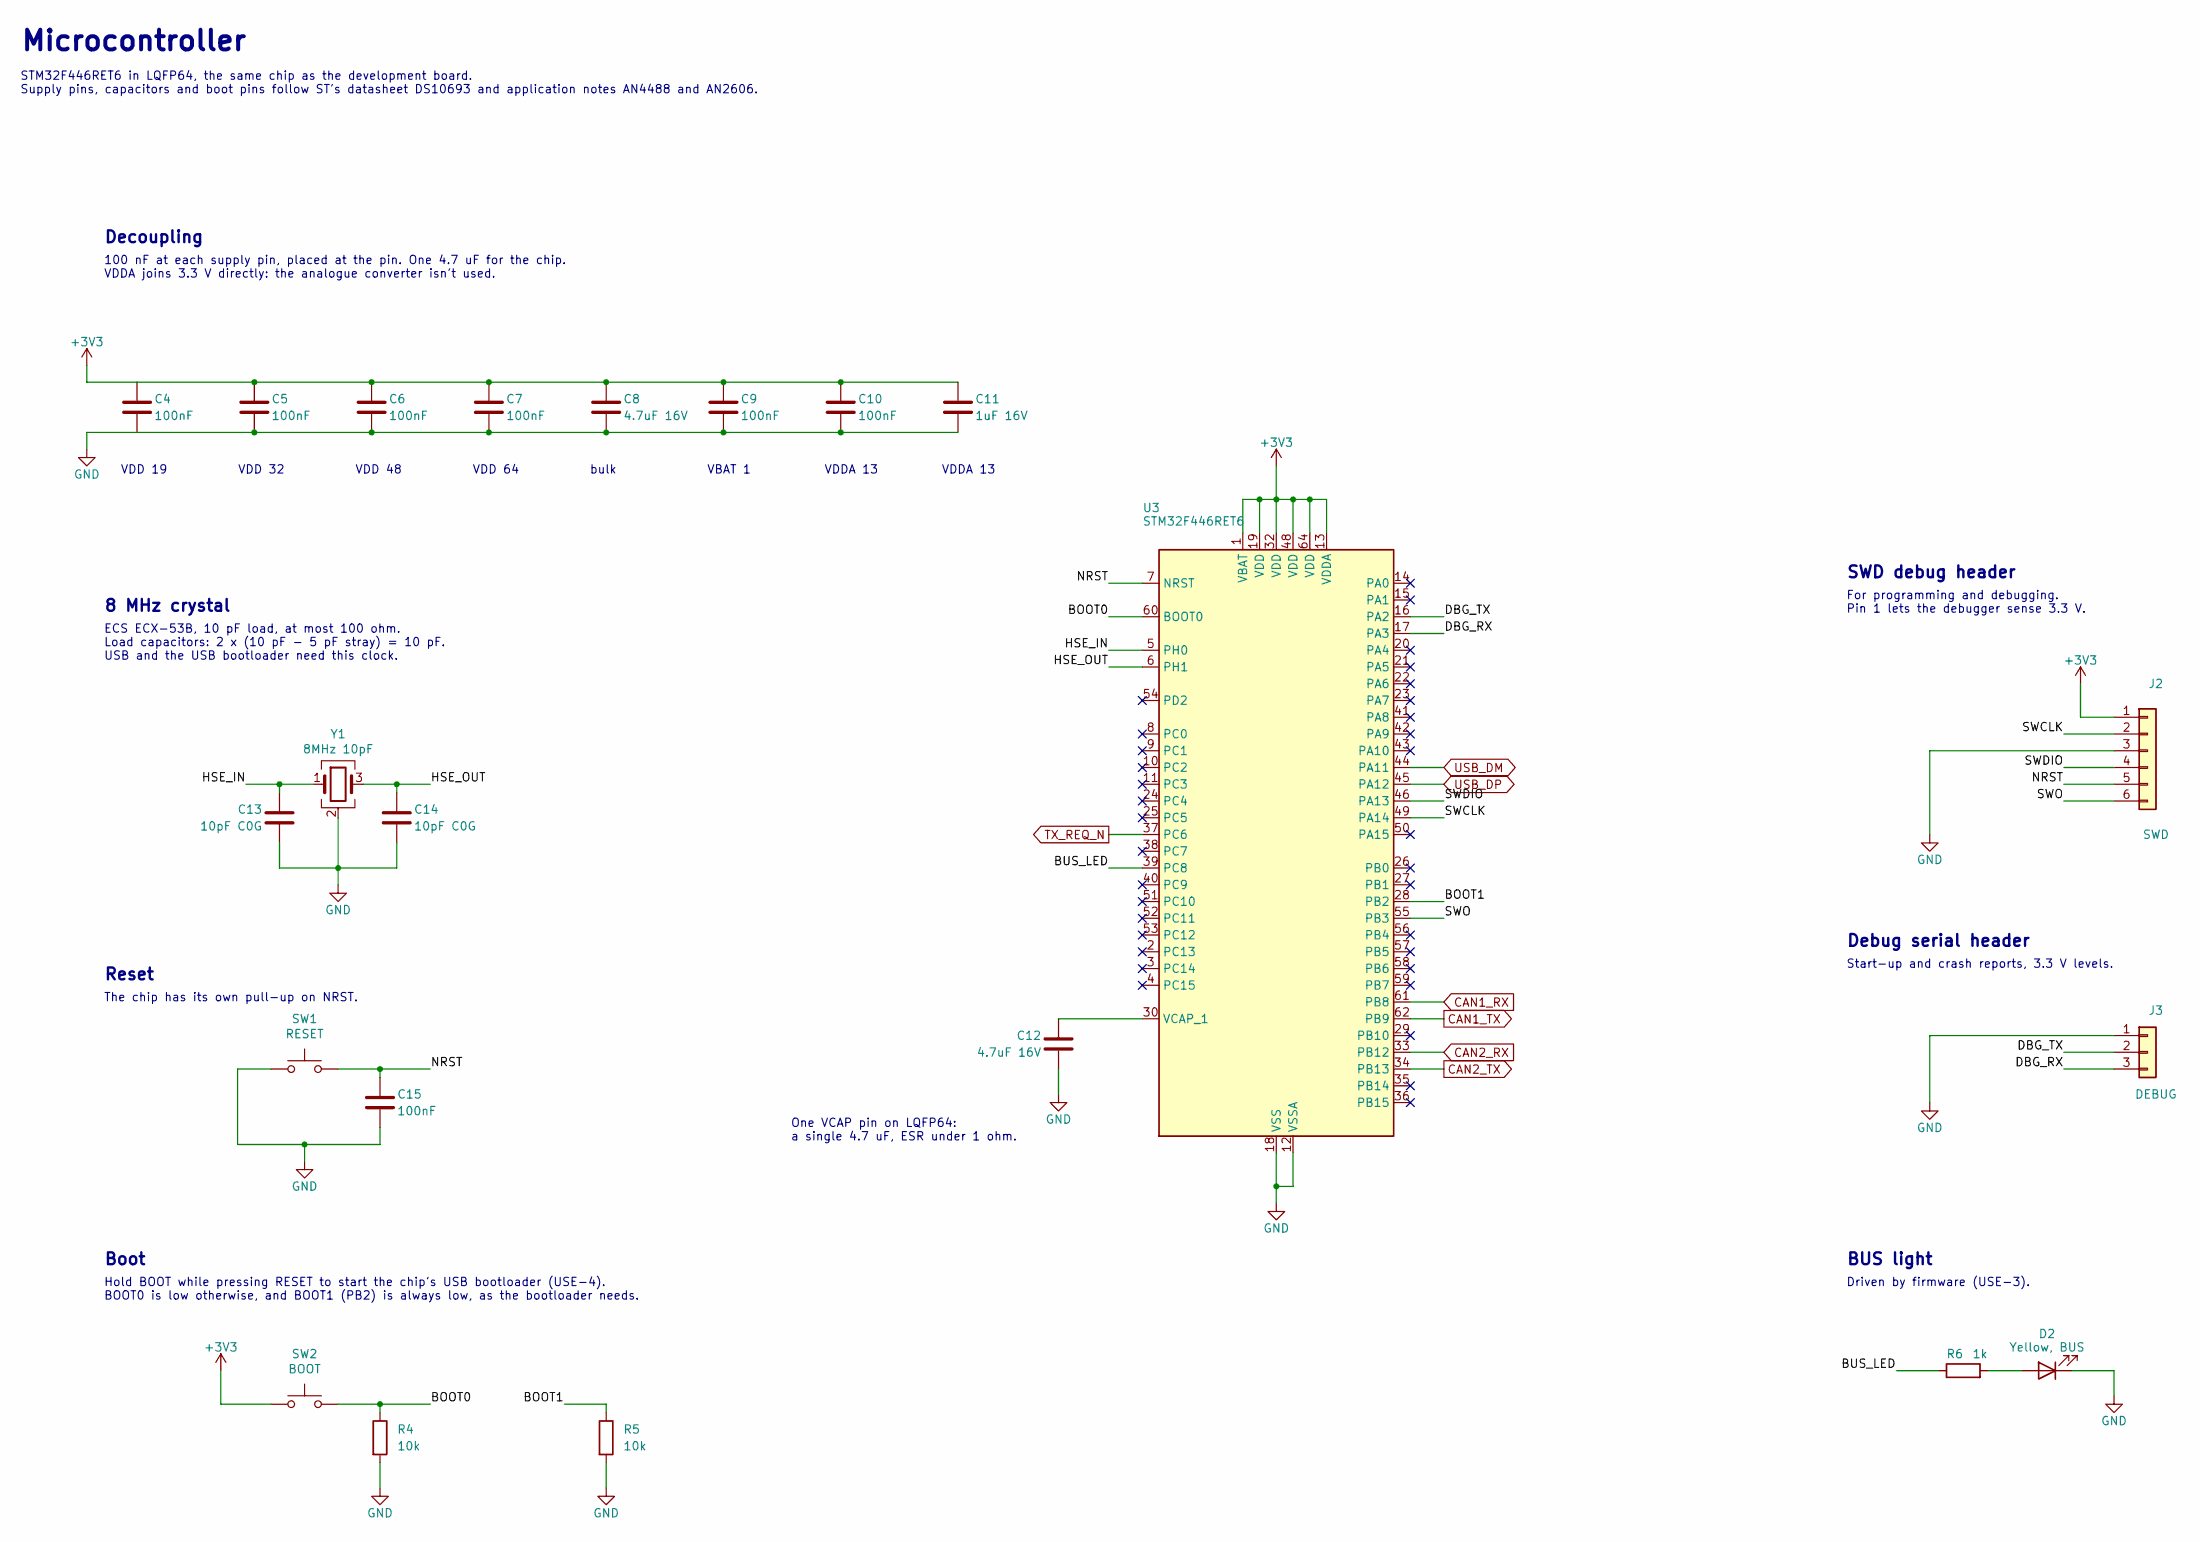
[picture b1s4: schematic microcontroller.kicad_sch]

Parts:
C4, C5, C6, C7, C9, C10, C15: 100nF; C_0603_1608Metric
C8, C12: 4.7uF 16V; C_0805_2012Metric
C11: 1uF 16V; C_0603_1608Metric
C13, C14: 10pF C0G; C_0603_1608Metric
D2: Yellow, BUS; LED_0603_1608Metric
J2: SWD; PinHeader_1x06_P2.54mm_Vertical
J3: DEBUG; PinHeader_1x03_P2.54mm_Vertical
R4, R5: 10k; R_0603_1608Metric
R6: 1k; R_0603_1608Metric
SW1: RESET; SW_SPST_PTS645Sx43SMTR92
SW2: BOOT; SW_SPST_PTS645Sx43SMTR92
U3: STM32F446RET6; LQFP-64_10x10mm_P0.5mm; MPN STM32F446RET6
Y1: 8MHz 10pF; Crystal_SMD_5032-4Pin_5.0x3.2mm; MPN ECS-80-10-30B-TR

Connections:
+3V3: C4.1, C5.1, C6.1, C7.1, C8.1, C9.1, C10.1, C11.1, J2.1, SW2.1, U3.1 (VBAT), U3.13 (VDDA), U3.19 (VDD), U3.32 (VDD), U3.48 (VDD), U3.64 (VDD); also elsewhere on the board
/Microcontroller/BOOT0: R4.1, SW2.2, U3.60 (BOOT0)
/Microcontroller/BOOT1: R5.1, U3.28 (PB2)
/Microcontroller/BUS_LED: R6.1, U3.39 (PC8)
/Microcontroller/DBG_RX: J3.3, U3.17 (PA3)
/Microcontroller/DBG_TX: J3.2, U3.16 (PA2)
/Microcontroller/HSE_IN: C13.1, U3.5 (PH0), Y1.1
/Microcontroller/HSE_OUT: C14.1, U3.6 (PH1), Y1.3
/Microcontroller/NRST: C15.1, J2.5, SW1.2, U3.7 (NRST)
/Microcontroller/SWCLK: J2.2, U3.49 (PA14)
/Microcontroller/SWDIO: J2.4, U3.46 (PA13)
/Microcontroller/SWO: J2.6, U3.55 (PB3)
CAN1_RX: U3.61 (PB8); also elsewhere on the board
CAN1_TX: U3.62 (PB9); also elsewhere on the board
CAN2_RX: U3.33 (PB12); also elsewhere on the board
CAN2_TX: U3.34 (PB13); also elsewhere on the board
GND: C4.2, C5.2, C6.2, C7.2, C8.2, C9.2, C10.2, C11.2, C12.2, C13.2, C14.2, C15.2, D2.1 (K), J2.3, J3.1, R4.2, R5.2, SW1.1, U3.12 (VSSA), U3.18 (VSS), U3.31 (VSS), U3.47 (VSS), U3.63 (VSS), Y1.2 (G), Y1.4 (G); also elsewhere on the board
unnamed: D2.2 (A), R6.2
unnamed: C12.1, U3.30 (VCAP_1)
TX_REQ_N: U3.37 (PC6); also elsewhere on the board
USB_DM: U3.44 (PA11); also elsewhere on the board
USB_DP: U3.45 (PA12); also elsewhere on the board

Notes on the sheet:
Microcontroller
Decoupling
VDDA 13
VDD 64
bulk
Reset
Boot
8 MHz crystal
VDD 48
VDD 19
One VCAP pin on LQFP64: a single 4.7 uF, ESR under 1 ohm.
BUS light
100 nF at each supply pin, placed at the pin. One 4.7 uF for the chip. VDDA joins 3.3 V directly: the analogue converter isn't used.
VBAT 1
For programming and debugging. Pin 1 lets the debugger sense 3.3 V.
STM32F446RET6 in LQFP64, the same chip as the development board. Supply pins, capacitors and boot pins follow ST's datasheet DS10693 and application notes AN4488 and AN2606.
SWD debug header
Hold BOOT while pressing RESET to start the chip's USB bootloader (USE-4). BOOT0 is low otherwise, and BOOT1 (PB2) is always low, as the bootloader needs.
Start-up and crash reports, 3.3 V levels.
VDD 32
Driven by firmware (USE-3).
The chip has its own pull-up on NRST.
Debug serial header
ECS ECX-53B, 10 pF load, at most 100 ohm. Load capacitors: 2 x (10 pF - 5 pF stray) = 10 pF. USB and the USB bootloader need this clock.

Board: 4 copper layers, 67 parts (0 on the bottom side), 40 nets, no tracks yet.

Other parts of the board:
H1, H2, H3, H4: M3; MountingHole_3.2mm_M3
